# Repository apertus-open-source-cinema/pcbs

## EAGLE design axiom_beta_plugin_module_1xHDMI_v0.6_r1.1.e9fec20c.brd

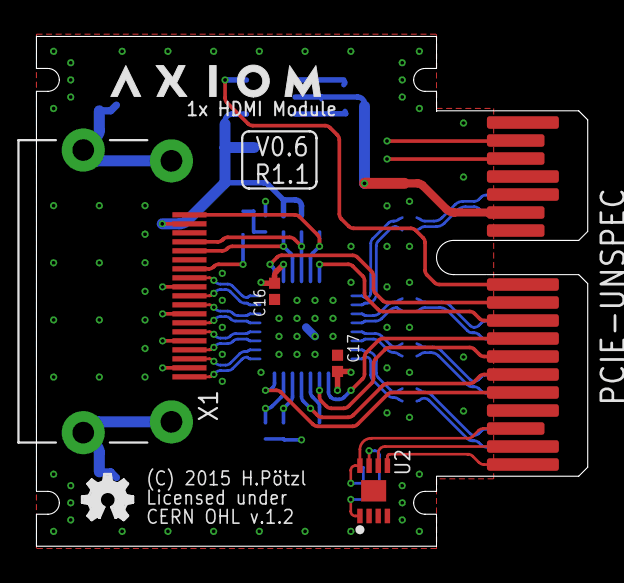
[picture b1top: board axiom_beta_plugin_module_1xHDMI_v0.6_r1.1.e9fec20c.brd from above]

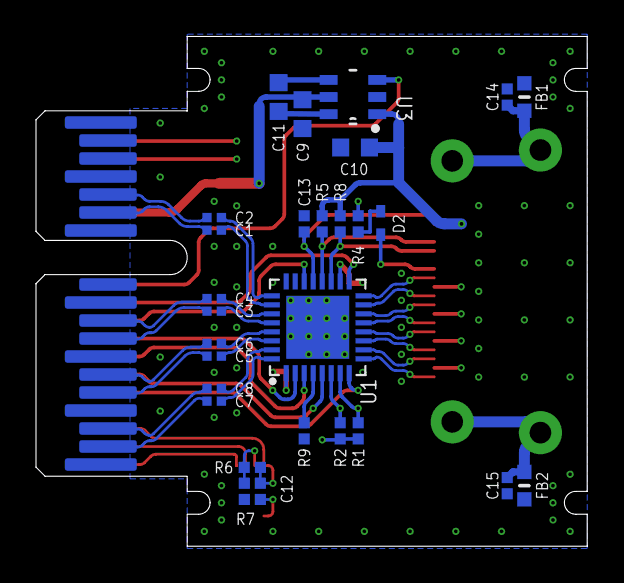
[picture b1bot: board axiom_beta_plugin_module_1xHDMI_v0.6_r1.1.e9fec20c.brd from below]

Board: 4 copper layers, 30.6 x 28.3 mm, 35 parts (28 on the bottom side), 50 nets.

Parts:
C1, C2, C3, C4, C5, C6, C7, C8: 100n; 0402-C
C9, C10, C11: 0603-B
C12: 0402-B
C13: 1-10n; 0402-B
C14, C15: 10n; 0402-B
C16, C17: 100n; 0402-B
D2: SOD523
FB1, FB2: _0603MP
LOGO2: OSHW_LOGO_FILLX0100-NT; OSHW_FILLX100_NOTEXT
PCIE-UNSPEC: PCIE-36-AXIOM
R1, R2, R5, R8: 2k2; 0402-B
R4, R6, R7: 0402-B
R9: 12k4; 0402-B
U1: PTN3363; HVQFN32
U2: BR24G04NUX; DFN200X300X100-9N
U3: REG710-DBV; DBV
U$1: AXIOM_LOGO459X70; AXIOM_LOGO_459X70
X1: HDMI-10029449; 10029449-X01XLF

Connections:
3V3: C9.1, C16.1, C17.1, PCIE-UNSPEC.B13, R1.1, R2.1, R4.1, U1.1, U1.18, U3.5
5V0: C10.1, R5.1, R8.1, U3.1, X1.18
!OE!: PCIE-UNSPEC.B10, U1.17
CLOCK_N: U1.16, X1.12
CLOCK_P: U1.15, X1.10
DATA0_N: U1.14, X1.9
DATA0_P: U1.13, X1.7
DATA1_N: U1.12, X1.6
DATA1_P: U1.11, X1.4
DATA2_N: U1.10, X1.3
DATA2_P: U1.9, X1.1
DDC_EN: PCIE-UNSPEC.B9, U1.22
DDET: PCIE-UNSPEC.B7, U1.3
EN: PCIE-UNSPEC.B11, U3.3
EQ0: PCIE-UNSPEC.B5, U1.8
EQ1: PCIE-UNSPEC.B8, U1.2
GND: C9.2, C10.2, C12.2, C13.2, C14.2, C15.2, C16.2, C17.2, FB1.2, FB2.2, PCIE-UNSPEC.A1, PCIE-UNSPEC.A4, PCIE-UNSPEC.A7, PCIE-UNSPEC.A10, PCIE-UNSPEC.A12, PCIE-UNSPEC.A15, PCIE-UNSPEC.A18, PCIE-UNSPEC.B15, PCIE-UNSPEC.B18, R7.2, R9.2, U1.24, U1.EP, U2.1, U2.2, U2.3, U2.4, U2.EP, U3.2, X1.2, X1.5, X1.8, X1.11, X1.17
HDMI_CEC: D2.C, X1.13
HDMI_HP: C13.1, U1.21, X1.19
HDMI_SCL: R8.2, U1.19, X1.15
HDMI_SDA: R5.2, U1.20, X1.16
I2C_V: C12.1, PCIE-UNSPEC.B3, R6.1, U2.8
IHP: PCIE-UNSPEC.B6, U1.5
IN_D1_N: C2.1, U1.25
IN_D1_P: C1.1, U1.26
IN_D2_N: C4.1, U1.27
IN_D2_P: C3.1, U1.28
IN_D3_N: C6.1, U1.29
IN_D3_P: C5.1, U1.30
IN_D4_N: C8.1, U1.31
IN_D4_P: C7.1, U1.32
ISCL: PCIE-UNSPEC.B16, R1.2, U1.7
ISDA: PCIE-UNSPEC.B17, R2.2, U1.6
LVDS_0_N: C8.2, PCIE-UNSPEC.A3
LVDS_0_P: C7.2, PCIE-UNSPEC.A2
LVDS_1_N: C6.2, PCIE-UNSPEC.A6
LVDS_1_P: C5.2, PCIE-UNSPEC.A5
LVDS_2_N: C4.2, PCIE-UNSPEC.A9
LVDS_2_P: C3.2, PCIE-UNSPEC.A8
LVDS_3_N: C2.2, PCIE-UNSPEC.A14
LVDS_3_P: C1.2, PCIE-UNSPEC.A13
unnamed: C11.1, U3.6
unnamed: C11.2, U3.4
unnamed: C14.1, FB1.1, X1.Z1, X1.Z2
unnamed: R6.2, R7.1, U2.7
unnamed: C15.1, FB2.1, X1.Z3, X1.Z4
unnamed: R9.1, U1.4
unnamed: D2.A, R4.2
SCL: PCIE-UNSPEC.B2, U2.6
SDA: PCIE-UNSPEC.B1, U2.5

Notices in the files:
axiom_beta_plugin_module_1xHDMI_v0.6_r1.1.e9fec20c.brd:
(C) 2015 H.Pötzl
Licensed under
CERN OHL v.1.2
parts and their libraries:
microbuilder: This work is placed in the public domain, and may be freely used for commercial and non-commercial work with the following conditions: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
